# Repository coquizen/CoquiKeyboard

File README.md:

<!--
*** Thanks for checking out this README Template. If you have a suggestion that would
*** make this better please fork the repo and create a pull request or simple open
*** an issue with the tag "enhancement".
*** Thanks again! Now go create something AMAZING! :D
-->

<!-- PROJECT SHIELDS -->
[![GPL License][license-shield]][license-url]

<!-- PROJECT LOGO -->
<br />
<p align="center">

  <h3 align="center">Coquí Keyboard</h3>

  <p align="center">
    A 40% compact keyboard with a full complement of alphas, including punctuation and symbols.
    <br />
    <a href="https://github.com/CaninoDev/Coqui"><strong>Explore the docs »</strong></a>
    <br />
    <br />
    <a href="https://github.com/othneildrew/Best-README-Template">View Demo</a>
    ·
    <a href="https://github.com/othneildrew/Best-README-Template/issues">Report Bug</a>
    ·
    <a href="https://github.com/othneildrew/Best-README-Template/issues">Request Feature</a>
  </p>
</p>

<!-- TABLE OF CONTENTS -->
## Table of Contents

- [Table of Contents](#table-of-contents)
- [About The Project](#about-the-project)
  - [Built With](#built-with)
- [Getting Started](#getting-started)
  - [Prerequisites](#prerequisites)
  - [Installation](#installation)
- [Usage](#usage)
- [Contributing](#contributing)
- [License](#license)
- [Contact](#contact)
- [Acknowledgements](#acknowledgements)

<!-- ABOUT THE PROJECT -->
## About The Project
Initial version 
[![Keyboard Layout][keyboard-layout]](https://github.com/CaninoDev/CoquiKeyboard)
 Finalized version
[![Keyboard_Layout_Finalized][keyboard-layout2]](https://i.imgur.com/WaaT3K5.png)
The coquí is a species of frog native to the island of Puerto Rico. Typically, they are no larger than a penny. They are so named for the loud mating call, _co-kee_. Similarly, this keyboard is a compact 40% keyboard with an extra column of two keys on the right intended for volume control. This keyboard is loosely based on  [Clueboard](https://clueboard.co/)

### Built With
The initial design was created with the help of [Keyboard Layout Editor](www.keyboard-layout-editor.com/) with input from @alexicon and @critray.
The schematic and pcb was created in [Kicad](http://kicad-pcb.org), an open source software.

<!-- GETTING STARTED -->
## Getting Started

_PLACEHOLDER_
### Prerequisites

_PLACEHOLDER_

### Installation

_PLACEHOLDER_
<!-- USAGE EXAMPLES -->
## Usage

_PLACEHOLDER_
<!-- CONTRIBUTING -->
## Contributing

_PLACEHOLDER_
<!-- LICENSE -->
## License

Distributed under the GPL License. See `LICENSE` for more information.

<!-- CONTACT -->
## Contact

<!-- ACKNOWLEDGEMENTS -->
## Acknowledgements

<!-- MARKDOWN LINKS & IMAGES -->

[license-shield]: https://img.shields.io/badge/license-GPL-blue.svg?style=flat-square
[license-url]: https://choosealicense.com/licenses/mit
[keyboard-layout]: https://i.imgur.com/pRL0Bjm.png\
[keyboard-layout2]: https://i.imgur.com/WaaT3K5.png

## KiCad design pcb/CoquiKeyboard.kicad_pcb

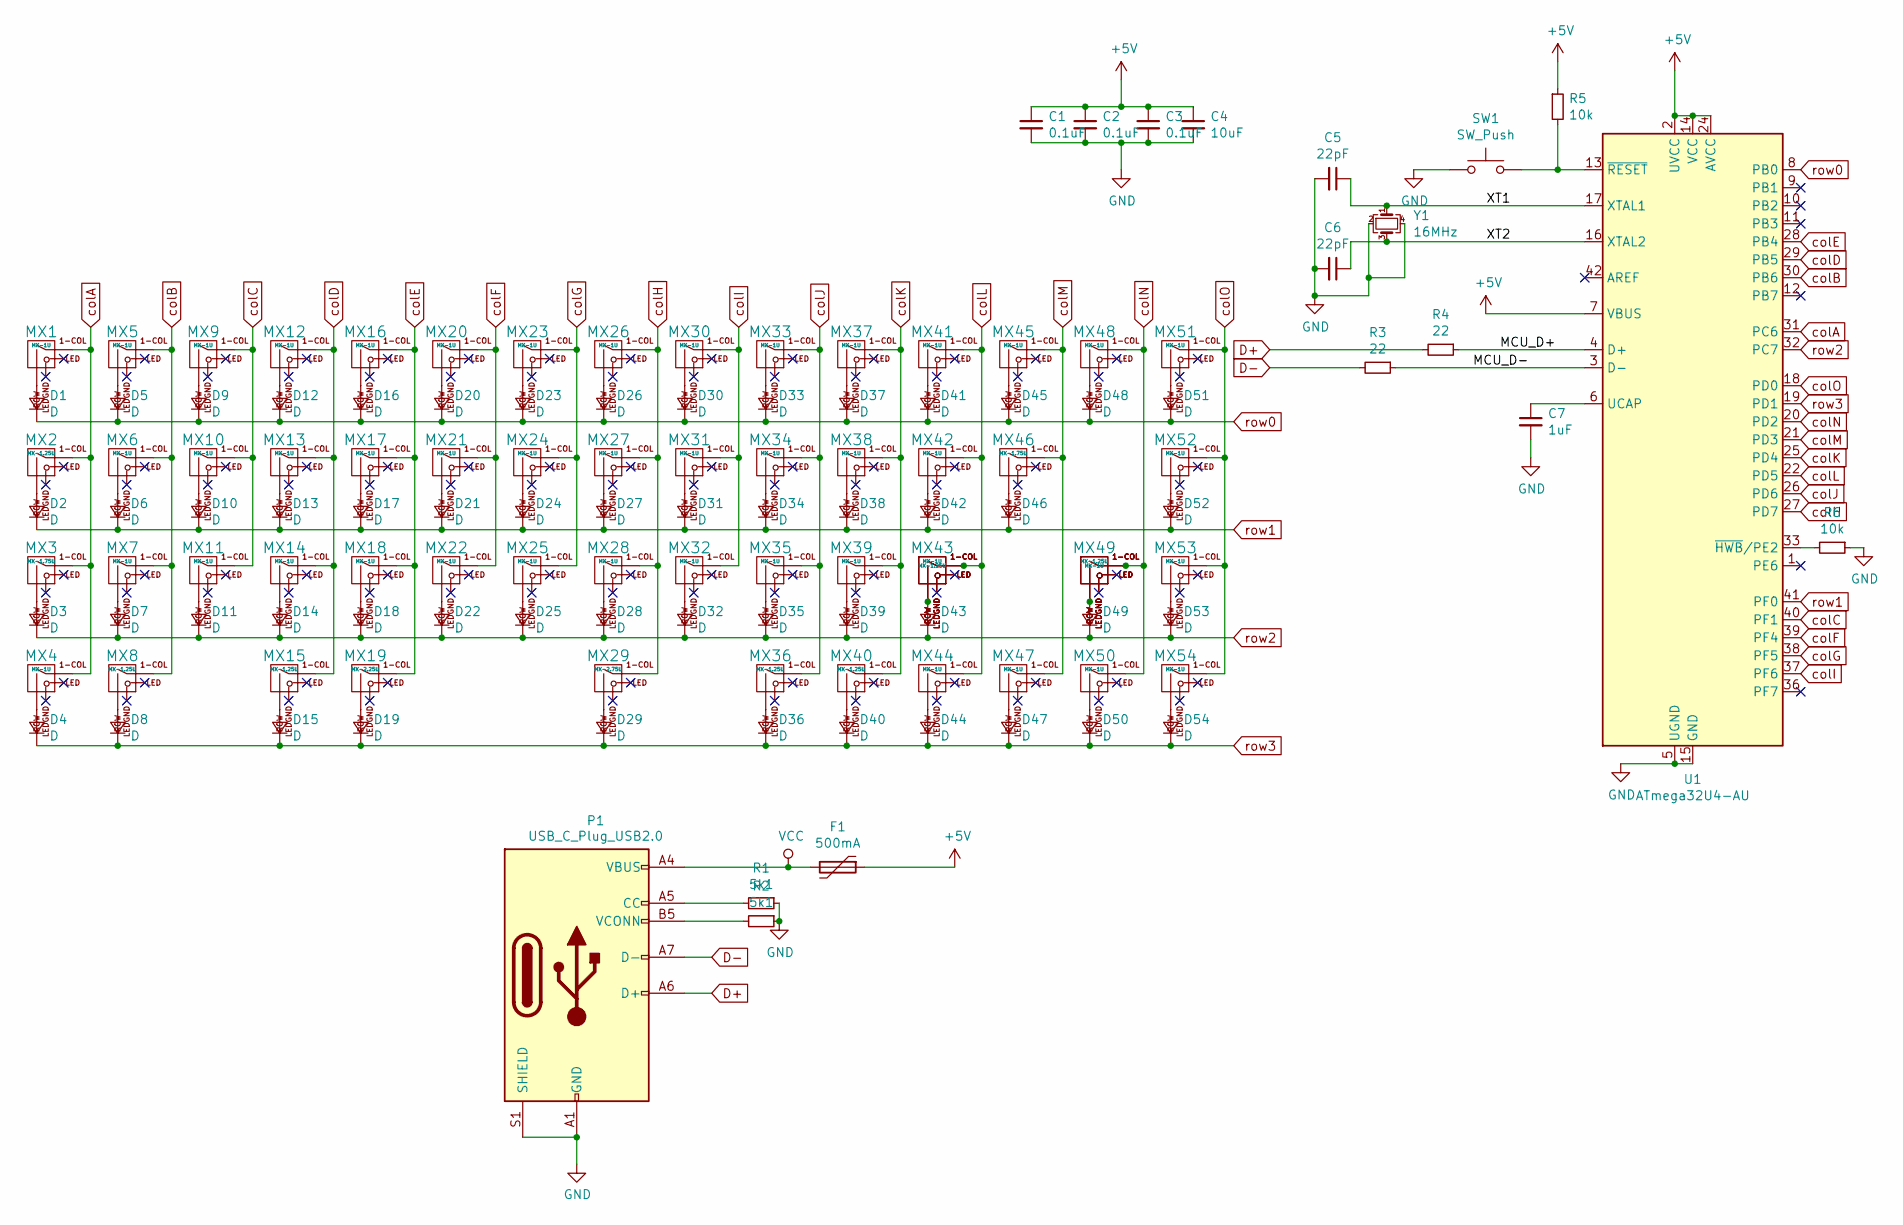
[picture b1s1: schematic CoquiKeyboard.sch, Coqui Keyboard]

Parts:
C1, C2, C3: 0.1uF; C_0805_2012Metric
C4: 10uF; C_0805_2012Metric
C5, C6: 22pF; C_0805_2012Metric
C7: 1uF; C_0805_2012Metric
D1, D2, D3, D4, D5, D6, D7, D8, D9, D10, D11, D12, D13, D14, D15, D16, D17, D18, D19, D20, D21, D22, D23, D24, D25, D26, D27, D28, D29, D30, D31, D32, D33, D34, D35, D36, D37, D38, D39, D40, D41, D42, D43, D44, D45, D46, D47, D48, D49, D50, D51, D52, D53, D54: D; D_SOD-123
F1: 500mA; Fuse_1206_3216Metric
MX1, MX4, MX5, MX6, MX7, MX9, MX10, MX11, MX12, MX13, MX14, MX16, MX17, MX18, MX20, MX21, MX22, MX23, MX24, MX25, MX26, MX27, MX28, MX30, MX31, MX32, MX33, MX34, MX35, MX37, MX38, MX39, MX41, MX42, MX42-1, MX43, MX44, MX45, MX47, MX48, MX50, MX51, MX52, MX53, MX54: MX-1U; MXOnly-1U-NoLED
MX2, MX8, MX15, MX36, MX40, MX41-1, MX49: MX-1.25U; MXOnly-1.25U-NoLED
MX3, MX46: MX-1.75U; MXOnly-1.75U-NoLED
MX19: MX-2.25U; MXOnly-2.25U-ReversedStabilizers-NoLED
MX29: MX-2.75U; MXOnly-2.75U-ReversedStabilizers-NoLED
P1: USB_C_Plug_USB2.0; USB_C_GCT_USB4085
R1, R2: 5k1; R_0805_2012Metric
R3, R4: 22; R_0805_2012Metric
R5, R6: 10k; R_0805_2012Metric
SW1: SW_Push; SKQG-1155865
U1: ATmega32U4-AU; TQFP-44_10x10mm_P0.8mm
Y1: 16MHz; Crystal_SMD_3225-4Pin_3.2x2.5mm

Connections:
+5V: C1.1, C2.1, C3.1, C4.1, F1.1, R5.1, U1.2 (UVCC), U1.7 (VBUS), U1.14 (VCC), U1.24 (AVCC), U1.34 (VCC), U1.44 (AVCC)
/MCU_D+: R4.1, U1.4 (D+)
/MCU_D-: R3.1, U1.3 (D-)
/XT1: C5.1, U1.17 (XTAL1), Y1.1
/XT2: C6.1, U1.16 (XTAL2), Y1.3
D+: P1.A6 (D+), R4.2
D-: P1.A7 (D-), R3.2
GND: C1.2, C2.2, C3.2, C4.2, C5.2, C6.2, C7.2, P1.A1 (GND), P1.A12 (GND), P1.B1 (GND), P1.B12 (GND), P1.S1 (SHIELD), R1.1, R2.1, R6.1, SW1.1, U1.5 (UGND), U1.15 (GND), U1.23 (GND), U1.35 (GND), U1.43 (GND), Y1.2, Y1.4
unnamed: C7.1, U1.6 (UCAP)
unnamed: D1.2 (A), MX1.2 (ROW)
unnamed: D2.2 (A), MX2.2 (ROW)
unnamed: D3.2 (A), MX3.2 (ROW)
unnamed: D4.2 (A), MX4.2 (ROW)
unnamed: D5.2 (A), MX5.2 (ROW)
unnamed: D6.2 (A), MX6.2 (ROW)
unnamed: D7.2 (A), MX7.2 (ROW)
unnamed: D8.2 (A), MX8.2 (ROW)
unnamed: D9.2 (A), MX9.2 (ROW)
unnamed: D10.2 (A), MX10.2 (ROW)
unnamed: D11.2 (A), MX11.2 (ROW)
unnamed: D12.2 (A), MX12.2 (ROW)
unnamed: D13.2 (A), MX13.2 (ROW)
unnamed: D14.2 (A), MX14.2 (ROW)
unnamed: D15.2 (A), MX15.2 (ROW)
unnamed: D16.2 (A), MX16.2 (ROW)
unnamed: D17.2 (A), MX17.2 (ROW)
unnamed: D18.2 (A), MX18.2 (ROW)
unnamed: D19.2 (A), MX19.2 (ROW)
unnamed: D20.2 (A), MX20.2 (ROW)
unnamed: D21.2 (A), MX21.2 (ROW)
unnamed: D22.2 (A), MX22.2 (ROW)
unnamed: D23.2 (A), MX23.2 (ROW)
unnamed: D24.2 (A), MX24.2 (ROW)
unnamed: D25.2 (A), MX25.2 (ROW)
unnamed: D26.2 (A), MX26.2 (ROW)
unnamed: D27.2 (A), MX27.2 (ROW)
unnamed: D28.2 (A), MX28.2 (ROW)
unnamed: D29.2 (A), MX29.2 (ROW)
unnamed: D30.2 (A), MX30.2 (ROW)
unnamed: D31.2 (A), MX31.2 (ROW)
unnamed: D32.2 (A), MX32.2 (ROW)
unnamed: D33.2 (A), MX33.2 (ROW)
unnamed: D34.2 (A), MX34.2 (ROW)
unnamed: D35.2 (A), MX35.2 (ROW)
unnamed: D36.2 (A), MX36.2 (ROW)
unnamed: D37.2 (A), MX37.2 (ROW)
unnamed: D38.2 (A), MX38.2 (ROW)
unnamed: D39.2 (A), MX39.2 (ROW)
unnamed: D40.2 (A), MX40.2 (ROW)
unnamed: D41.2 (A), MX41.2 (ROW)
unnamed: D42.2 (A), MX42.2 (ROW)
unnamed: D43.2 (A), MX41-1.2 (ROW), MX43.2 (ROW)
unnamed: D44.2 (A), MX44.2 (ROW)
unnamed: D45.2 (A), MX45.2 (ROW)
unnamed: D46.2 (A), MX46.2 (ROW)
unnamed: D47.2 (A), MX47.2 (ROW)
unnamed: D48.2 (A), MX48.2 (ROW)
unnamed: D49.2 (A), MX42-1.1 (ROW), MX49.1 (ROW)
unnamed: D50.2 (A), MX50.2 (ROW)
unnamed: D51.2 (A), MX51.1 (ROW)
unnamed: D52.2 (A), MX52.1 (ROW)
unnamed: D53.2 (A), MX53.1 (ROW)
unnamed: D54.2 (A), MX54.1 (ROW)
unnamed: P1.A5 (CC), R1.2
unnamed: P1.B5 (VCONN), R2.2
unnamed: R5.2, SW1.2, U1.13 (~RESET)
unnamed: R6.2, U1.33 (~HWB~/PE2)
VCC: F1.2, P1.A4 (VBUS), P1.A9 (VBUS), P1.B4 (VBUS), P1.B9 (VBUS)
colA: MX1.1 (COL), MX2.1 (COL), MX3.1 (COL), MX4.1 (COL), U1.31 (PC6)
colB: MX5.1 (COL), MX6.1 (COL), MX7.1 (COL), MX8.1 (COL), U1.30 (PB6)
colC: MX9.1 (COL), MX10.1 (COL), MX11.1 (COL), U1.40 (PF1)
colD: MX12.1 (COL), MX13.1 (COL), MX14.1 (COL), MX15.1 (COL), U1.29 (PB5)
colE: MX16.1 (COL), MX17.1 (COL), MX18.1 (COL), MX19.1 (COL), U1.28 (PB4)
colF: MX20.1 (COL), MX21.1 (COL), MX22.1 (COL), U1.39 (PF4)
colG: MX23.1 (COL), MX24.1 (COL), MX25.1 (COL), U1.38 (PF5)
colH: MX26.1 (COL), MX27.1 (COL), MX28.1 (COL), MX29.1 (COL), U1.27 (PD7)
colI: MX30.1 (COL), MX31.1 (COL), MX32.1 (COL), U1.37 (PF6)
colJ: MX33.1 (COL), MX34.1 (COL), MX35.1 (COL), MX36.1 (COL), U1.26 (PD6)
colK: MX37.1 (COL), MX38.1 (COL), MX39.1 (COL), MX40.1 (COL), U1.25 (PD4)
colL: MX41.1 (COL), MX41-1.1 (COL), MX42.1 (COL), MX43.1 (COL), MX44.1 (COL), U1.22 (PD5)
colM: MX45.1 (COL), MX46.1 (COL), MX47.1 (COL), U1.21 (PD3)
colN: MX42-1.2 (COL), MX48.1 (COL), MX49.2 (COL), MX50.1 (COL), U1.20 (PD2)
colO: MX51.2 (COL), MX52.2 (COL), MX53.2 (COL), MX54.2 (COL), U1.18 (PD0)
row0: D1.1 (K), D5.1 (K), D9.1 (K), D12.1 (K), D16.1 (K), D20.1 (K), D23.1 (K), D26.1 (K), D30.1 (K), D33.1 (K), D37.1 (K), D41.1 (K), D45.1 (K), D48.1 (K), D51.1 (K), U1.8 (PB0)
row1: D2.1 (K), D6.1 (K), D10.1 (K), D13.1 (K), D17.1 (K), D21.1 (K), D24.1 (K), D27.1 (K), D31.1 (K), D34.1 (K), D38.1 (K), D42.1 (K), D46.1 (K), D52.1 (K), U1.41 (PF0)
row2: D3.1 (K), D7.1 (K), D11.1 (K), D14.1 (K), D18.1 (K), D22.1 (K), D25.1 (K), D28.1 (K), D32.1 (K), D35.1 (K), D39.1 (K), D43.1 (K), D49.1 (K), D53.1 (K), U1.32 (PC7)
row3: D4.1 (K), D8.1 (K), D15.1 (K), D19.1 (K), D29.1 (K), D36.1 (K), D40.1 (K), D44.1 (K), D47.1 (K), D50.1 (K), D54.1 (K), U1.19 (PD1)

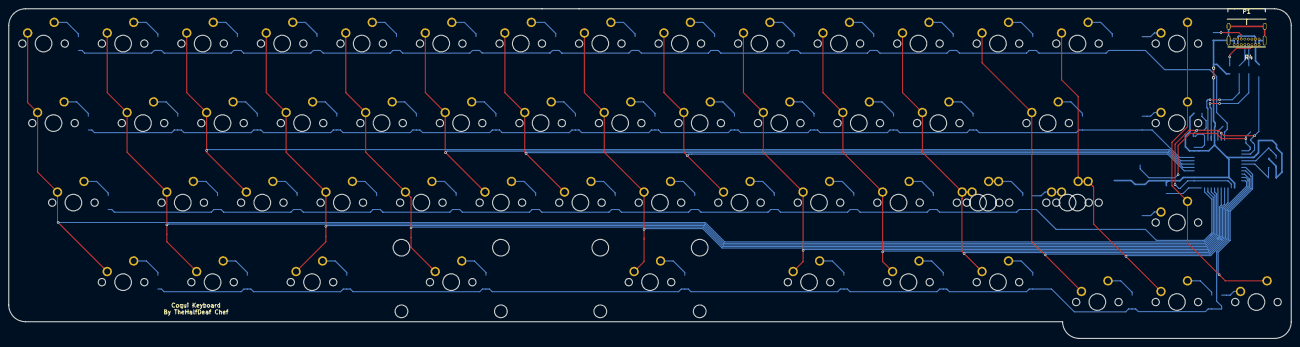
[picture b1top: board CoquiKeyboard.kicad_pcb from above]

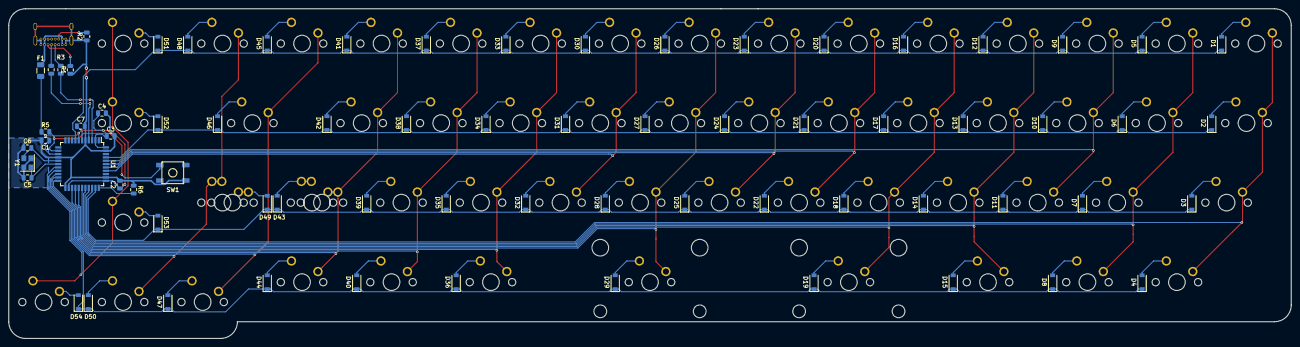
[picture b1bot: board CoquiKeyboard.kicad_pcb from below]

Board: 2 copper layers, 307.2 x 79.0 mm, 128 parts (71 on the bottom side), 87 nets.

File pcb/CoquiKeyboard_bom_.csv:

Component,Description,Part,References,Value,Footprint,Quantity Per PCB,Datasheet,LCSC Link
1,"Unpolarized capacitor, small symbol",C_Small,C1 C2 C3,0.1uF,C_0805_2012Metric,3,~,https://lcsc.com/product-detail/Others_CCTC-TCC0805X7R104M50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
2,"Unpolarized capacitor, small symbol",C_Small,C4,10uF,C_0805_2012Metric,1,~,https://lcsc.com/product-detail/Others_Samsung-Electro-Mecha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
3,"Unpolarized capacitor, small symbol",C_Small,C7,1uF,C_0805_2012Metric,1,~,https://lcsc.com/product-detail/Multilayer-Ceramic-Capacitor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
4,"Unpolarized capacitor, small symbol",C_Small,C5 C6,22pF,C_0805_2012Metric,2,~,https://lcsc.com/product-detail/New-Arrivals_CCTC-TCC0805COG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
5,"Diode, small symbol",D_Small,D1 D2 D3 D4 D5 D6 D7 D8 D9 D10 D11 D12 D13 D14 D15 D16 D17 D18 D19 D20 D21 D22 D23 D24 D25 D26 D27 D28 D29 D30 D31 D32 D33 D34 D35 D36 D37 D38 D39 D40 D41 D42 D43 D44 D45 D46 D47 D48 D49 D50 D51 D52 D53 D54,D,D_SOD-123,54,~,https://lcsc.com/product-detail/Switching-Diode_IN4148W_C181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
6,"Resettable fuse, polymeric positive temperature coefficient",Polyfuse,F1,500mA,Fuse_1206_3216Metric,1,~,https://lcsc.com/product-detail/Others_Littelfuse_1206L050YR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
7,,MX-1.25U,MX16 MX41-1 MX45 MX46 MX49 MX50,MX-1.25U,MXOnly-1.25U-NoLED,6,,
8,,MX-1.25U-FLIPPED,MX42,MX-1.25U,MXOnly-1.25U-NoLED,1,,
9,,MX-1.75U,MX28 MX30,MX-1.75U,MXOnly-1.75U-NoLED,2,,
10,,MX-1U,MX1 MX2 MX3 MX4 MX5 MX6 MX7 MX8 MX9 MX10 MX11 MX12 MX13 MX14 MX17 MX18 MX19 MX20 MX21 MX22 MX23 MX24 MX25 MX26 MX27 MX31 MX32 MX33 MX34 MX35 MX36 MX37 MX38 MX39 MX40 MX41 MX44 MX51 MX52 MX53,MX-1U,MXOnly-1U-NoLED,40,,
11,,MX-1U-FLIPPED,MX15 MX29 MX42-1 MX43 MX54,MX-1U,MXOnly-1U-NoLED,5,,
12,,MX-2.25U,MX47,MX-2.25U,MXOnly-2.25U-ReversedStabilizers-NoLED,1,,
13,,MX-2.75U,MX48,MX-2.75U,MXOnly-2.75U-ReversedStabilizers-NoLED,1,,
14,"Resistor, small symbol",R_Small,R1 R4,10k,R_0805_2012Metric,2,~,https://lcsc.com/product-detail/Chip-Resistor-Surface-Mount_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
15,"Resistor, small symbol",R_Small,R2 R3,22,R_0805_2012Metric,2,~,https://lcsc.com/product-detail/Chip-Resistor-Surface-Mount_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
16,,SW_Push-Switch,SW1,SW_Push,SKQG-1155865,1,~,https://lcsc.com/product-detail/Tactile-Switches_ALPS_SKQGAB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
17,"16MHz, 32kB Flash, 2.5kB SRAM, 1kB EEPROM, USB 2.0, TQFP-44",ATmega32U4-AU,U1,ATmega32U4-AU,TQFP-44_10x10mm_P0.8mm,1,http://ww1.microchip.com/downloads/en/DeviceDoc/Atmel-7766-8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,https://lcsc.com/product-detail/ATMEL-AVR_ATMEL_ATMEGA32U4-A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
18,,USB-Mini-B_ LCSC-C46398,USB1,USB Mini,USB-Mini-B_ LCSC-C46398,1,,https://lcsc.com/product-detail/USB-Connectors_Jing-Extensio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
19,,Crystal_GND24_Small-Device,Y1,16MHz,Crystal_SMD_3225-4Pin_3.2x2.5mm,1,~,https://lcsc.com/product-detail/SMD-Crystals_EPSON_X1E000021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
,,,,,,,,
,,,,,,,,
,,,,,,,,
,,,,,,,,
,,,,,,,,
Component Groups:,19,,,,,,,
Component Count:,126,,,,,,,
Fitted Components:,126,,,,,,,
Number of PCBs:,1,,,,,,,
Total components:,126,,,,,,,
Schematic Version:,,,,,,,,
Schematic Date:,,,,,,,,
BoM Date:,5/26/2019 14:05,,,,,,,
Schematic Source:,E:\Desktop\Peioris Boards\pcb comms\CoquiKeyboard\pcb\CoquiKeyboard.sch,,,,,,,
KiCad Version:,Eeschema (5.0.1)-4,,,,,,,

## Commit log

2019-05-16 add library submodule
2019-05-16 initialize KiCAD project
2019-05-16 add atmega32u4
2019-05-16 attach power and ground to mcu
2019-05-16 add resistors to USB pins
2019-05-16 add capacitors to UCAP
2019-05-17 add decoupling capacitors
2019-05-17 bind VBUS to 5V
2019-05-17 add crystal with load capacitors
2019-05-17 add pull up resistor between reset and +5v
2019-05-17 place global nets on the USB lines
2019-05-17 connect VBUS to Polyfuse
2019-05-17 add 50 switches
2019-05-17 connect anode of the diode of each row
2019-05-17 reformat schematics
2019-05-18 more reformatting
2019-05-18 label components
2019-05-18 connect diodes to switches
2019-05-18 realignment of switches
2019-05-18 draw matrices
2019-05-18 label matrix
2019-05-18 assign footprint to schematics
2019-05-18 generate net list
2019-05-18 load netlist to create pcb
2019-05-18 fix keysize error
2019-05-18 fix positioning of switches
2019-05-19 Edit a gramatical error in README.md
2019-05-19 arrange switches to keyboard layout
2019-05-19 allign keyboard to grid
2019-05-19 align resistors with their keys
2019-05-20 clean up ratsnet
2019-05-22 refine some alignment
2019-05-22 add Keebio-Parts pretty library
2019-05-22 create PCB board outline
2019-05-25 update readme with new design
2019-05-26 updated files
2019-05-28 add logo as footprint
2019-05-28 update schematics to use with newer USB-C
2019-05-28 replaced old footprint with new
2019-05-31 add plate files
2019-06-02 reconnect resistors and diodes to USB C
2019-06-06 create alternate location for usbc draft
2019-06-08 cleanup
2019-06-09 connected remainder of diodes, network closed
2019-06-10 repopulate the BOM file
2019-06-13 complete board for prototyping
2019-06-21 readjust the pcb cutout to compensate for stab footprint
2019-07-03 cleanup files
